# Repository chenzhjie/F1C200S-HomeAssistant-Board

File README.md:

# F1C200S-HomeAssistant-Board

这是一个 F1C200S 的 Linux 开发板。

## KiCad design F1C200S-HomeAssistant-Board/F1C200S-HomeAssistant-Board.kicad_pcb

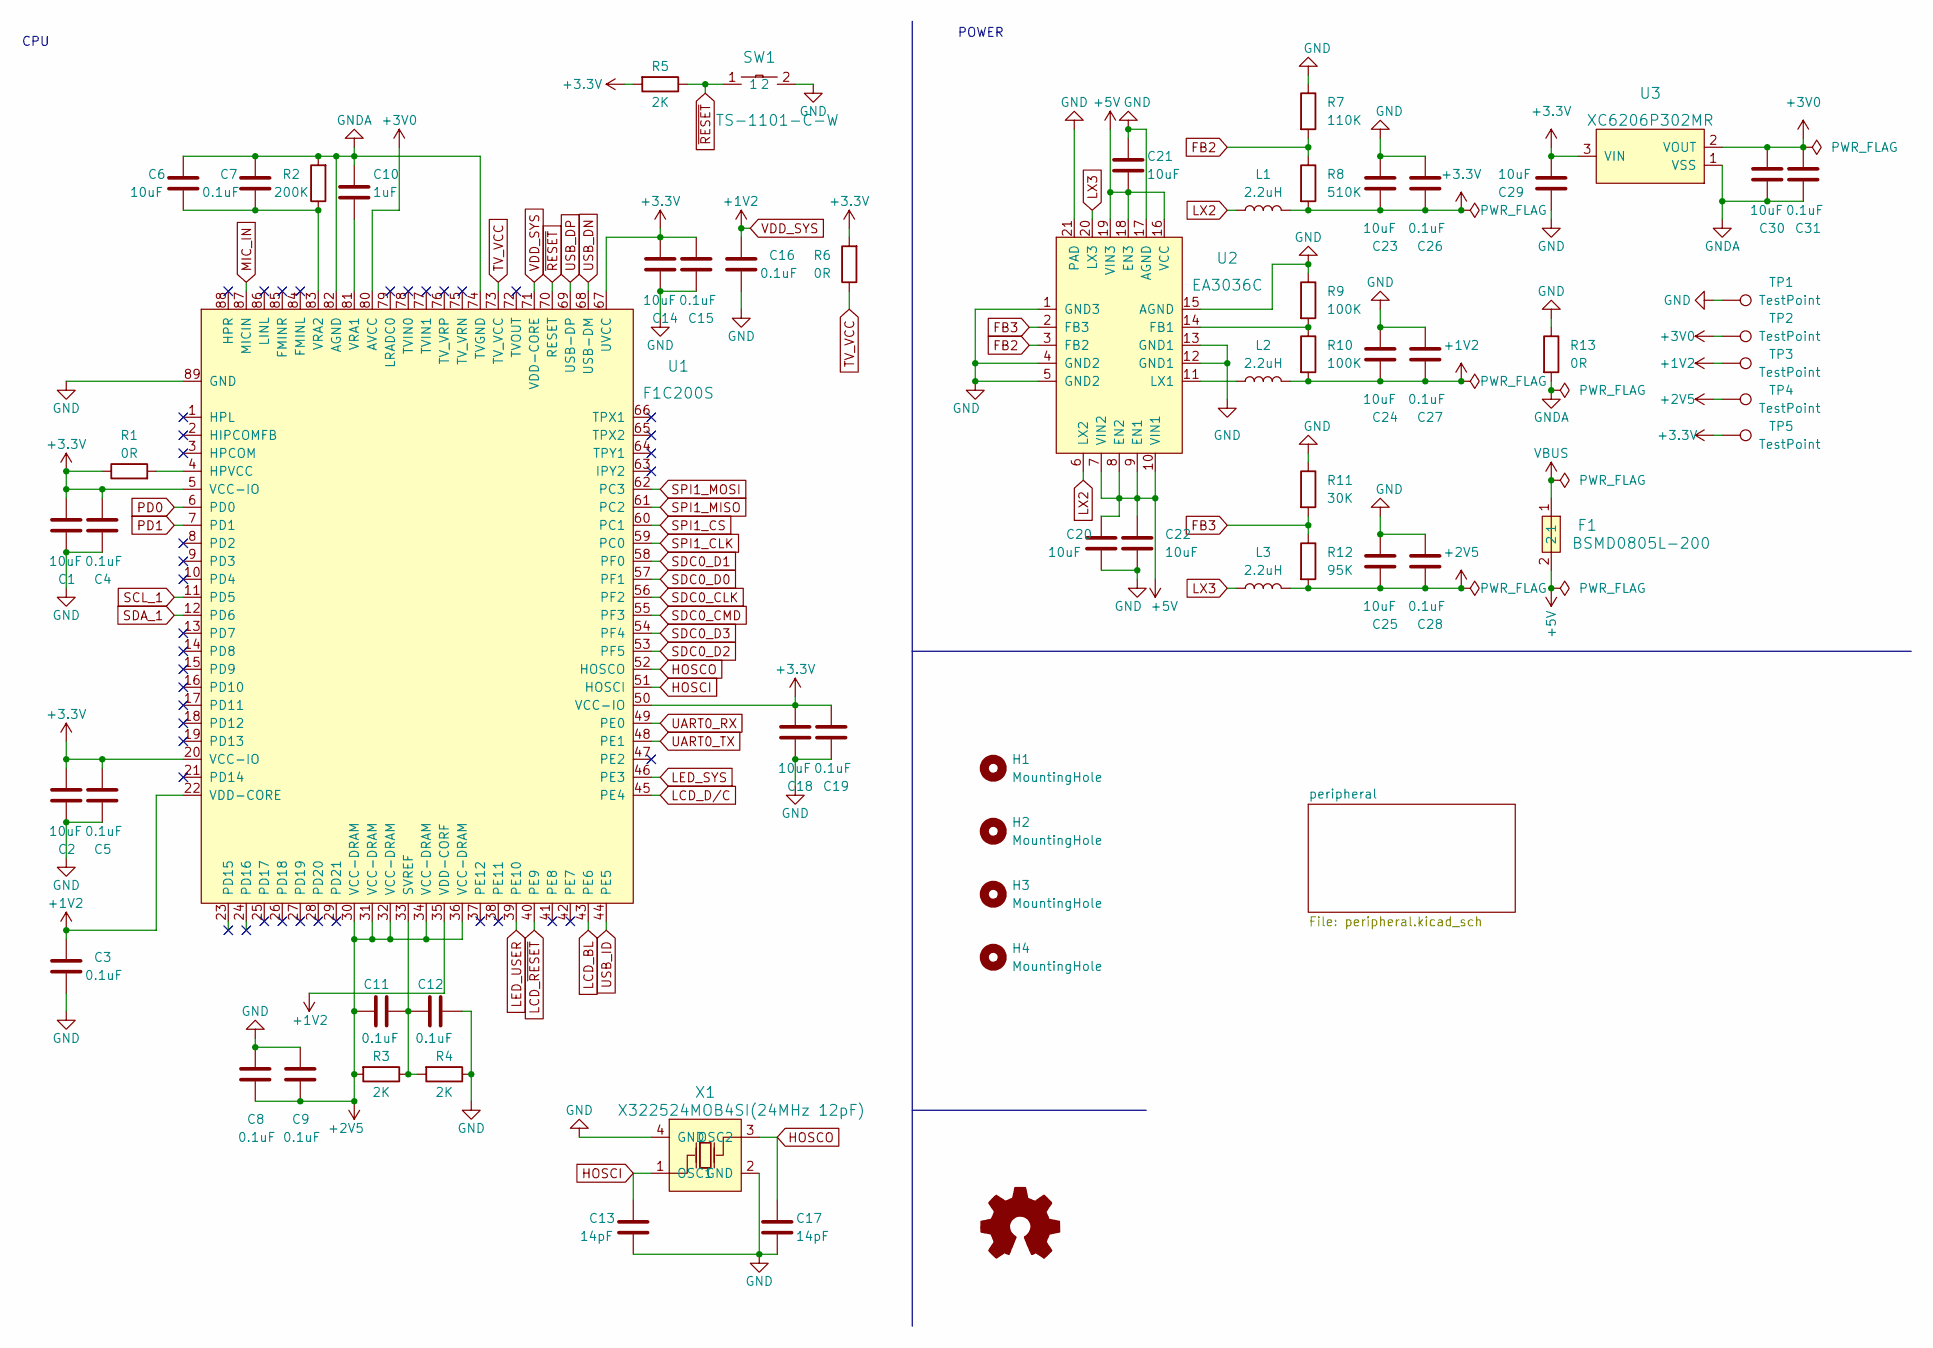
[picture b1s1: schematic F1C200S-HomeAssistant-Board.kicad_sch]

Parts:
C1, C2, C6, C14, C18, C20, C21, C22, C23, C24, C25, C29, C30: 10uF; C_0402_1005Metric_Pad0.74x0.62mm_HandSolder; LCSC Part C15525
C3, C4, C5, C7, C8, C9, C11, C12, C15, C16, C19, C26, C27, C28, C31: 0.1uF; C_0402_1005Metric_Pad0.74x0.62mm_HandSolder; LCSC Part C60474
C10: 1uF; C_0402_1005Metric_Pad0.74x0.62mm_HandSolder; LCSC Part C107372
C13, C17: 14pF; C_0402_1005Metric_Pad0.74x0.62mm_HandSolder; LCSC Part C3037644
F1: BSMD0805L-200; F0805; LCSC Part C2757931
H1, H2, H3, H4: MountingHole; MountingHole_2.7mm_M2.5
L1, L2, L3: 2.2uH; L0603; LCSC Part C394950
R1, R6, R13: 0R; R_0402_1005Metric_Pad0.72x0.64mm_HandSolder; LCSC Part C21376
R2: 200K; R_0402_1005Metric_Pad0.72x0.64mm_HandSolder; LCSC Part C114763
R3, R4, R5: 2K; R_0402_1005Metric_Pad0.72x0.64mm_HandSolder; LCSC Part C60488
R7: 110K; R_0402_1005Metric_Pad0.72x0.64mm_HandSolder; LCSC Part C138065
R8: 510K; R_0402_1005Metric_Pad0.72x0.64mm_HandSolder; LCSC Part C137961
R9, R10: 100K; R_0402_1005Metric_Pad0.72x0.64mm_HandSolder; LCSC Part C60491
R11: 30K; R_0402_1005Metric_Pad0.72x0.64mm_HandSolder; LCSC Part C138008
R12: 95K; R_0402_1005Metric_Pad0.72x0.64mm_HandSolder
SW1: TS-1101-C-W; SW-SMD_L6.0-W3.3-LS8.0; LCSC Part C318938
TP1, TP2, TP3, TP4, TP5: TestPoint; TestPoint_Pad_D1.0mm
U1: F1C200S; QFN-88_L10.0-W10.0-P0.40-BL-EP6.75; LCSC Part C2879851
U2: EA3036C; WQFN-20_L3.0-W3.0-P0.40-BL-EP; LCSC Part C570857
U3: XC6206P302MR; SOT-23-3L_L2.9-W1.6-P1.90-LS2.8-BL; LCSC Part C2904833
X1: X322524MOB4SI(24MHz 12pF); CRYSTAL-SMD_4P-L3.2-W2.5-BL; LCSC Part C70590

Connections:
+2V5: C8.2, C9.2, C11.1, C25.2, C28.2, L3.2, R3.2, R12.2, TP4.1, U1.30 (VCC-DRAM), U1.31 (VCC-DRAM), U1.32 (VCC-DRAM), U1.34 (VCC-DRAM), U1.36 (VCC-DRAM)
+3V0: C30.1, C31.1, TP2.1, U1.80 (AVCC), U3.2 (VOUT); also elsewhere on the board
+5V: C20.1, C21.1, C22.1, F1.2, U2.7 (VIN2), U2.8 (EN2), U2.9 (EN1), U2.10 (VIN1), U2.16 (VCC), U2.18 (EN3), U2.19 (VIN3); also elsewhere on the board
FB2: R7.2, R8.1, U2.3 (FB2)
FB3: R11.2, R12.1, U2.2 (FB3)
GND: C1.2, C2.2, C3.2, C4.2, C5.2, C8.1, C9.1, C12.2, C13.2, C14.2, C15.2, C16.2, C17.2, C18.2, C19.2, C20.2, C21.2, C22.2, C23.1, C24.1, C25.1, C26.1, C27.1, C28.1, C29.2, R4.1, R7.1, R9.1, R11.1, R13.1, SW1.2, TP1.1, U1.89 (GND), U2.1 (GND3), U2.4 (GND2), U2.5 (GND2), U2.12 (GND1), U2.13 (GND1), U2.15 (AGND), U2.17 (AGND), U2.21 (PAD), X1.2 (GND), X1.4 (GND); also elsewhere on the board
GNDA: C6.1, C7.1, C10.1, C30.2, C31.2, R2.2, R13.2, U1.74 (TVGND), U1.82 (AGND), U3.1 (VSS); also elsewhere on the board
HOSCI: C13.1, U1.51 (HOSCI), X1.1 (OSC1)
HOSCO: C17.1, U1.52 (HOSCO), X1.3 (OSC2)
LCD_BL: U1.43 (PE6); also elsewhere on the board
LCD_D/C: U1.45 (PE4); also elsewhere on the board
LCD_~RESET: U1.40 (PE9); also elsewhere on the board
LED_SYS: U1.46 (PE3); also elsewhere on the board
LED_USER: U1.39 (PE10); also elsewhere on the board
LX2: L1.1, U2.6 (LX2)
LX3: L3.1, U2.20 (LX3)
MIC_IN: U1.87 (MICIN); also elsewhere on the board
unnamed: C6.2, C7.2, R2.1, U1.83 (VRA2)
unnamed: C10.2, U1.81 (VRA1)
unnamed: C11.2, C12.1, R3.1, R4.2, U1.33 (SVREF)
unnamed: L2.1, U2.11 (LX1)
unnamed: R1.2, U1.4 (HPVCC)
unnamed: R9.2, R10.1, U2.14 (FB1)
PD0: U1.6 (PD0); also elsewhere on the board
PD1: U1.7 (PD1); also elsewhere on the board
SCL_1: U1.11 (PD5); also elsewhere on the board
SDA_1: U1.12 (PD6); also elsewhere on the board
SDC0_CLK: U1.56 (PF2); also elsewhere on the board
SDC0_CMD: U1.55 (PF3); also elsewhere on the board
SDC0_D0: U1.57 (PF1); also elsewhere on the board
SDC0_D1: U1.58 (PF0); also elsewhere on the board
SDC0_D2: U1.53 (PF5); also elsewhere on the board
SDC0_D3: U1.54 (PF4); also elsewhere on the board
SPI1_CLK: U1.59 (PC0); also elsewhere on the board
SPI1_CS: U1.60 (PC1); also elsewhere on the board
SPI1_MISO: U1.61 (PC2); also elsewhere on the board
SPI1_MOSI: U1.62 (PC3); also elsewhere on the board
TV_VCC: R6.1, U1.73 (TV_VCC)
UART0_RX: U1.49 (PE0); also elsewhere on the board
UART0_TX: U1.48 (PE1); also elsewhere on the board
USB_DN: U1.68 (USB-DM); also elsewhere on the board
USB_DP: U1.69 (USB-DP); also elsewhere on the board
USB_ID: U1.44 (PE5); also elsewhere on the board
VBUS: F1.1; also elsewhere on the board
VDD_SYS: C3.1, C16.1, C24.2, C27.2, L2.2, R10.2, TP3.1, U1.22 (VDD-CORE), U1.35 (VDD-CORF), U1.71 (VDD-CORE)
~RESET: R5.1, SW1.1, U1.70 (RESET)

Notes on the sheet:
POWER
CPU

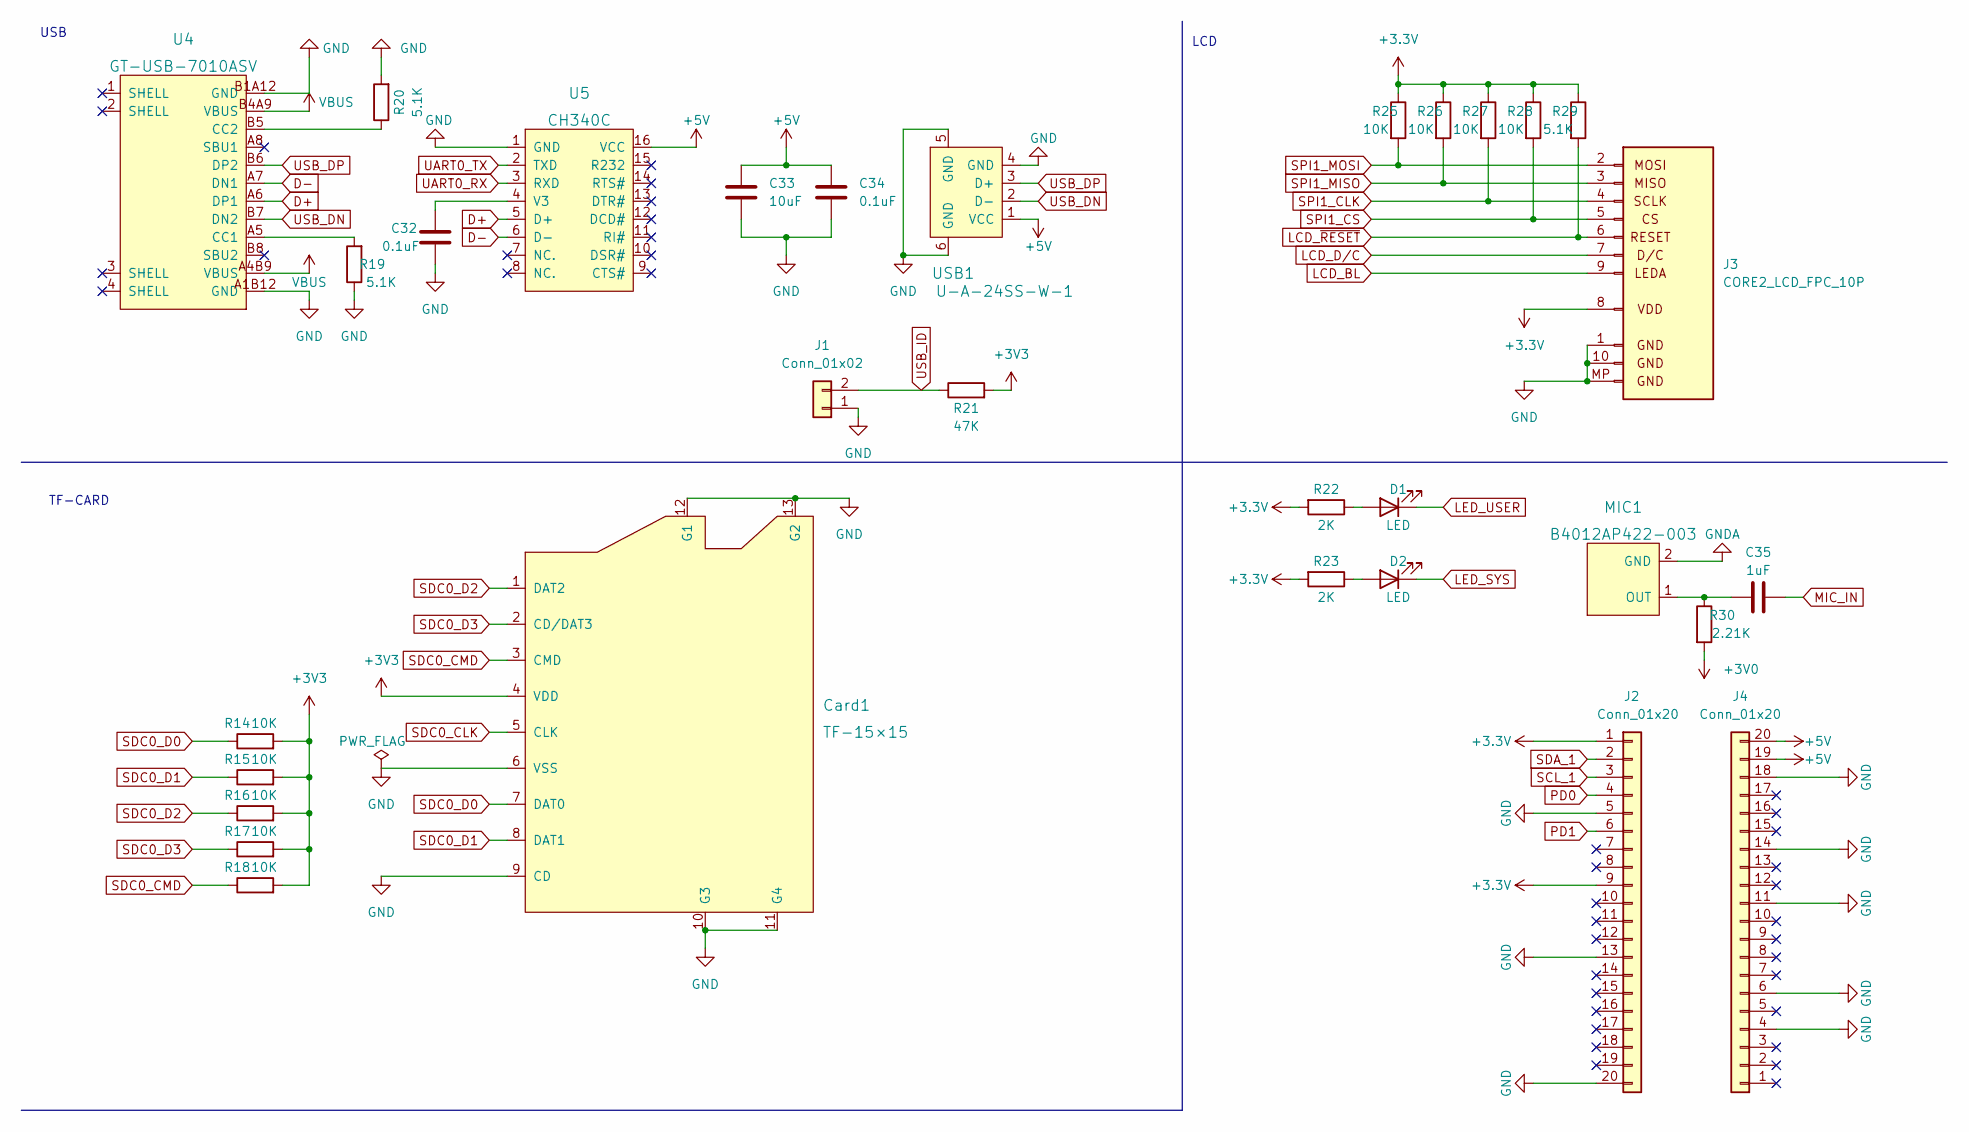
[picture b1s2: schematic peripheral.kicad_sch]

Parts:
C32, C34: 0.1uF; C_0402_1005Metric_Pad0.74x0.62mm_HandSolder; LCSC Part C60474
C33: 10uF; C_0402_1005Metric_Pad0.74x0.62mm_HandSolder; LCSC Part C15525
C35: 1uF; C_0402_1005Metric_Pad0.74x0.62mm_HandSolder; LCSC Part C107372
Card1: TF-15×15; TF-SMD_TF-15-15; LCSC Part C111196
D1: LED; LED_0402_1005Metric_Pad0.77x0.64mm_HandSolder; LCSC Part C434446
D2: LED; LED_0402_1005Metric_Pad0.77x0.64mm_HandSolder; LCSC Part C71911
J1: Conn_01x02; PinHeader_1x02_P2.54mm_Vertical
J2, J4: Conn_01x20; PinHeader_1x20_P2.54mm_Vertical
J3: CORE2_LCD_FPC_10P; TE_1-1734839-0_1x10-1MP_P0.5mm_Horizontal
MIC1: B4012AP422-003; MIC-TH_BD4.0-P1.40-D0.3-L; LCSC Part C233791
R14, R15, R16, R17, R18, R25, R26, R27, R28: 10K; R_0402_1005Metric_Pad0.72x0.64mm_HandSolder; LCSC Part C144807
R19, R20, R29: 5.1K; R_0402_1005Metric_Pad0.72x0.64mm_HandSolder; LCSC Part C105872
R21: 47K; R_0402_1005Metric_Pad0.72x0.64mm_HandSolder; LCSC Part C144757
R22, R23: 2K; R_0402_1005Metric_Pad0.72x0.64mm_HandSolder; LCSC Part C60488
R30: 2.21K; R_0402_1005Metric_Pad0.72x0.64mm_HandSolder; LCSC Part C416375
U4: GT-USB-7010ASV; USB-C-SMD_G-SWITCH_GT-USB-7010ASV; LCSC Part C2988369
U5: CH340C; SOP-16_L10.0-W3.9-P1.27-LS6.0-BL; LCSC Part C84681
USB1: U-A-24SS-W-1; USB-A-SMD_U-A-24SS-W-1; LCSC Part C283549

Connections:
+3V0: R30.2; also elsewhere on the board
+5V: C33.1, C34.1, J4.19, J4.20, U5.16 (VCC), USB1.1 (VCC); also elsewhere on the board
D+: U4.A6 (DP1), U5.5 (D+)
D-: U4.A7 (DN1), U5.6 (D-)
GND: C32.2, C33.2, C34.2, Card1.6 (VSS), Card1.9 (CD), Card1.10 (G3), Card1.11 (G4), Card1.12 (G1), Card1.13 (G2), J1.1, J2.5, J2.13, J2.20, J3.1, J3.10, J3.MP (Pin_10), J4.4, J4.6, J4.11, J4.14, J4.18, R19.1, R20.2, U4.A1B12 (GND), U4.B1A12 (GND), U5.1 (GND), USB1.4 (GND), USB1.5 (GND), USB1.6 (GND); also elsewhere on the board
GNDA: MIC1.2 (GND); also elsewhere on the board
LCD_BL: J3.9; also elsewhere on the board
LCD_D/C: J3.7; also elsewhere on the board
LCD_~RESET: J3.6, R29.2; also elsewhere on the board
LED_SYS: D2.1 (K); also elsewhere on the board
LED_USER: D1.1 (K); also elsewhere on the board
MIC_IN: C35.2; also elsewhere on the board
unnamed: C32.1, U5.4 (V3)
unnamed: C35.1, MIC1.1 (OUT), R30.1
unnamed: D1.2 (A), R22.1
unnamed: D2.2 (A), R23.1
unnamed: R19.2, U4.A5 (CC1)
unnamed: R20.1, U4.B5 (CC2)
PD0: J2.4; also elsewhere on the board
PD1: J2.6; also elsewhere on the board
SCL_1: J2.3; also elsewhere on the board
SDA_1: J2.2; also elsewhere on the board
SDC0_CLK: Card1.5 (CLK); also elsewhere on the board
SDC0_CMD: Card1.3 (CMD), R18.1; also elsewhere on the board
SDC0_D0: Card1.7 (DAT0), R14.1; also elsewhere on the board
SDC0_D1: Card1.8 (DAT1), R15.1; also elsewhere on the board
SDC0_D2: Card1.1 (DAT2), R16.1; also elsewhere on the board
SDC0_D3: Card1.2 (CD/DAT3), R17.1; also elsewhere on the board
SPI1_CLK: J3.4, R27.2; also elsewhere on the board
SPI1_CS: J3.5, R28.2; also elsewhere on the board
SPI1_MISO: J3.3, R26.2; also elsewhere on the board
SPI1_MOSI: J3.2, R25.2; also elsewhere on the board
UART0_RX: U5.3 (RXD); also elsewhere on the board
UART0_TX: U5.2 (TXD); also elsewhere on the board
USB_DN: U4.B7 (DN2), USB1.2 (D-); also elsewhere on the board
USB_DP: U4.B6 (DP2), USB1.3 (D+); also elsewhere on the board
USB_ID: J1.2, R21.1; also elsewhere on the board
VBUS: U4.A4B9 (VBUS), U4.B4A9 (VBUS); also elsewhere on the board

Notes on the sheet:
LCD
TF-CARD
USB

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
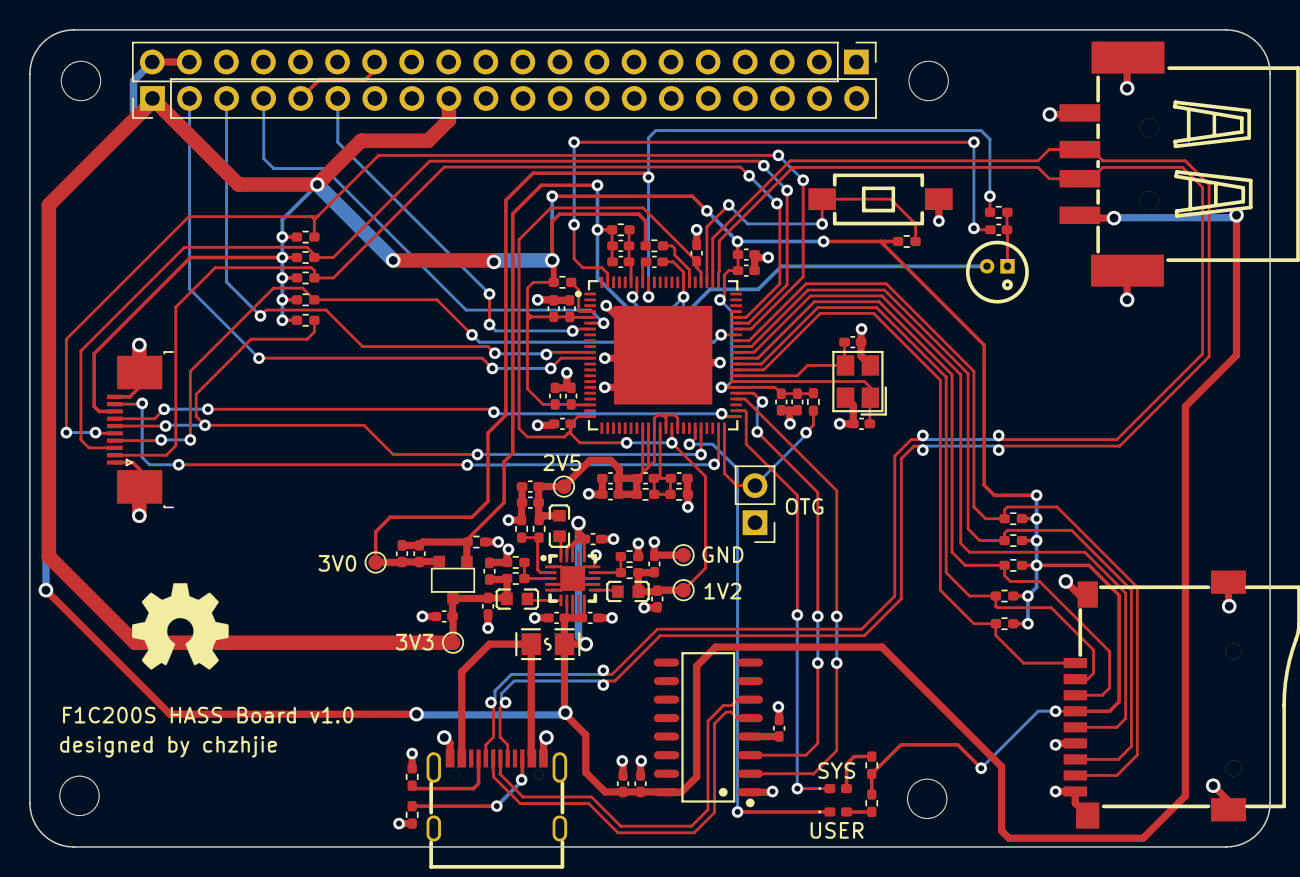
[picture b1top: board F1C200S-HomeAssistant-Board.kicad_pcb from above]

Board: 2 copper layers, 85.0 x 56.0 mm, 93 parts (0 on the bottom side), 55 nets.

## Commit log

2022-08-28 init
2022-09-03 docs: 更新制作文件
2022-09-04 docs: BOM 表修正
2022-09-04 docs: 更新 BOM 表
